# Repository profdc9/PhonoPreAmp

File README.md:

# Phono Preamplifier

This is a PCB for Bill Christie's phono preamplifier as detailed in his article "Build an External Phonograph Preamplifier" in the 07/13 issue of audioXpress.  The original article can be found at

https://audioxpress.com/article/You-Can-DIY-Build-an-External-Phono-Preamplifier

https://audioxpress.com/assets/upload/files/BillChristieExternalPhonoPreampAXJul2013.pdf

The changes made are as follows.  The LME49740, which is not available anymore, has been replaced with two LM4562 op amps.  22 pF Miller capacitors are placed to stabilize the LM4562 from oscillation.  The signal grounds for the two channels are isolated from the power ground by hum breaker resistors.

This is a two-channel PCB layout for the LM3886-based Super Gain Clone by Bob Cordell.  It can be found in Chapter 27 in his book "Audio Amplifiers."

The PCB is made available under the Creative Commons CC-BY-SA 4.0 license.

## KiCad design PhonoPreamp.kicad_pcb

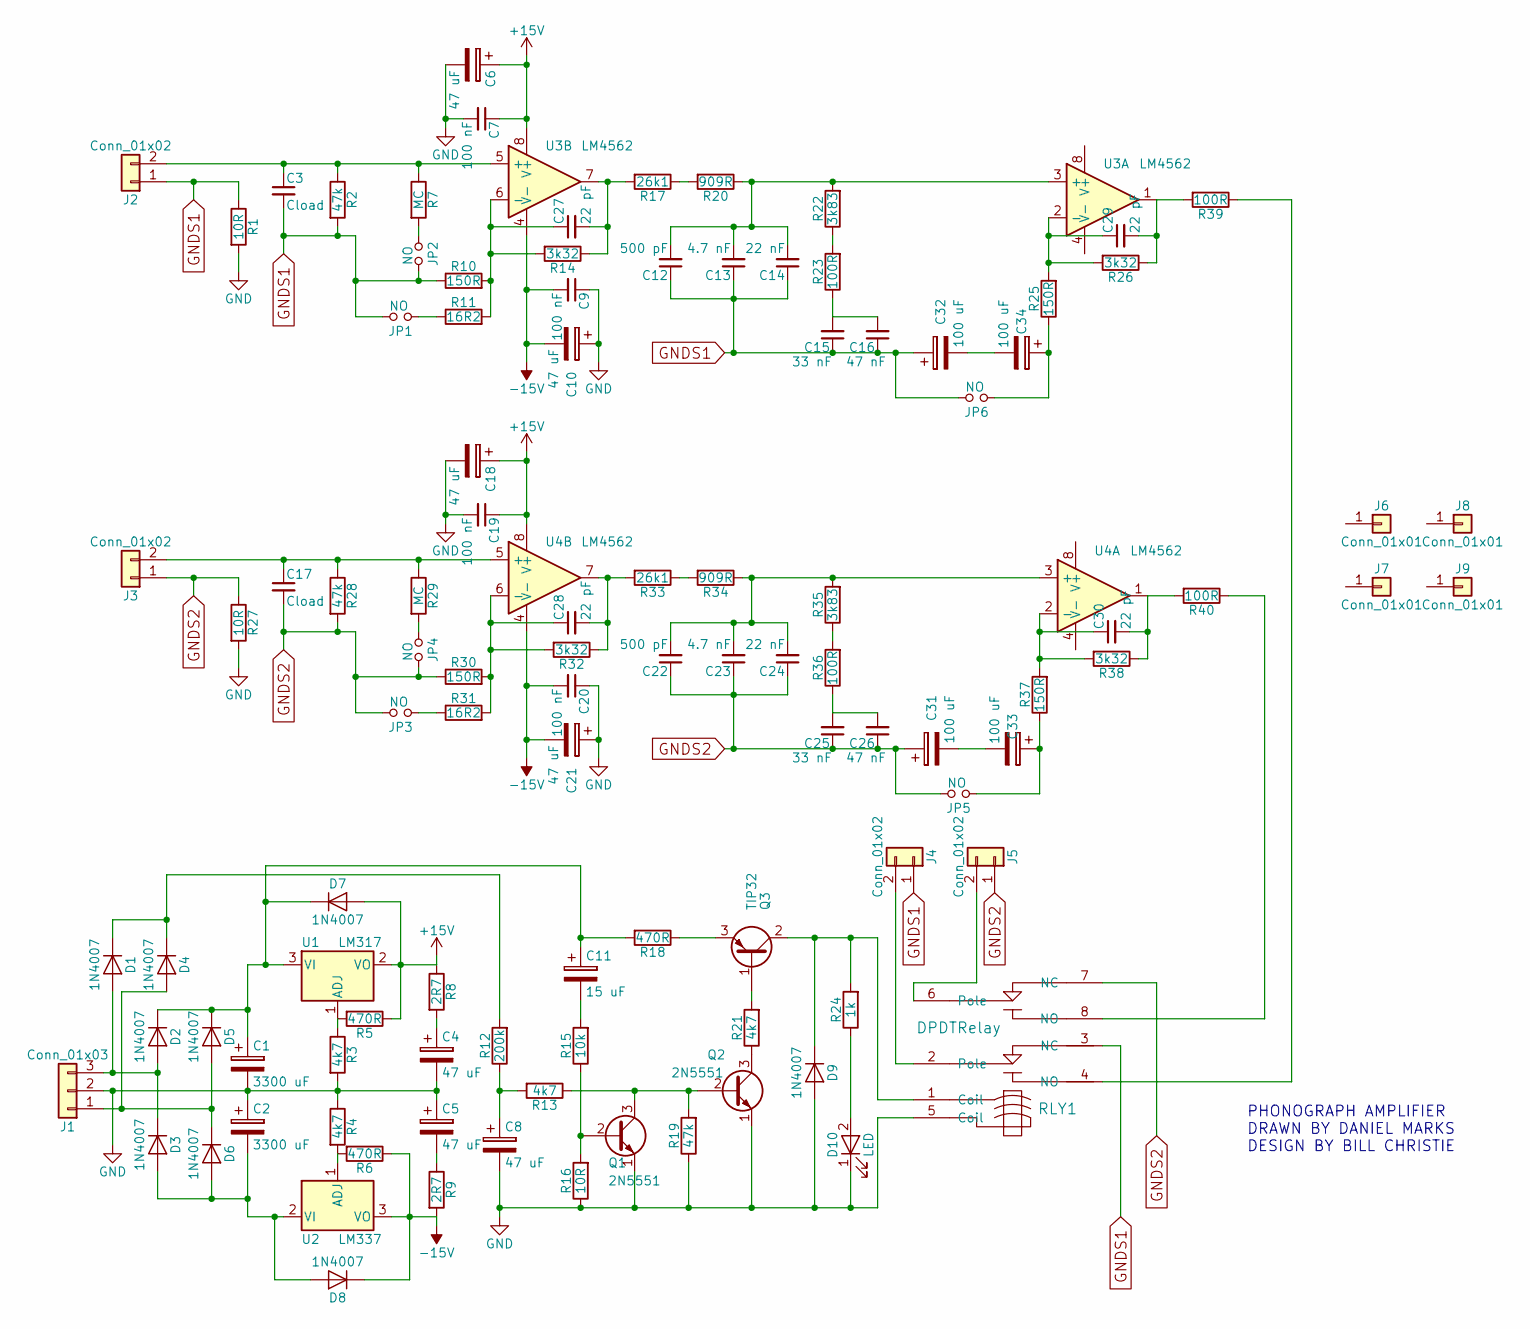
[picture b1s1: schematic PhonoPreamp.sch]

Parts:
C1, C2: 3300 uF; CP_Radial_D14.0mm_P5.00mm
C3, C17: Cload; C_Disc_D5.0mm_W2.5mm_P5.00mm
C4, C5: 47 uF; CP_Radial_D14.0mm_P5.00mm
C6, C8, C10, C18, C21: 47 uF; CP_Radial_D7.5mm_P2.50mm
C7, C9, C19, C20: 100 nF; C_Disc_D5.0mm_W2.5mm_P5.00mm
C11: 15 uF; CP_Radial_D7.5mm_P2.50mm
C12, C22: 500 pF; C_Disc_D5.0mm_W2.5mm_P5.00mm
C13, C23: 4.7 nF; C_Disc_D5.0mm_W2.5mm_P5.00mm
C14, C24: 22 nF; C_Disc_D5.0mm_W2.5mm_P5.00mm
C15, C25: 33 nF; C_Disc_D5.0mm_W2.5mm_P5.00mm
C16, C26: 47 nF; C_Disc_D5.0mm_W2.5mm_P5.00mm
C27, C28, C29, C30: 22 pF; C_Disc_D5.0mm_W2.5mm_P5.00mm
C31, C32, C33, C34: 100 uF; CP_Radial_D7.5mm_P2.50mm
D1, D2, D3, D4, D5, D6, D7, D8, D9: 1N4007; D_DO-41_SOD81_P7.62mm_Horizontal
D10: LED; LED_D5.0mm
J1: Conn_01x03; TerminalBlock_bornier-3_P5.08mm
J2, J3, J4, J5: Conn_01x02; TerminalBlock_bornier-2_P5.08mm
J6, J7, J8, J9: Conn_01x01; 1pin
JP1, JP2, JP3, JP4, JP5, JP6: NO; Pin_Header_Straight_1x02_Pitch2.54mm
Q1, Q2: 2N5551; TO-92_Inline_Wide
Q3: TIP32; TO-220-3_Vertical
R1, R16, R27: 10R; R_Axial_DIN0207_L6.3mm_D2.5mm_P7.62mm_Horizontal
R2, R19, R28: 47k; R_Axial_DIN0207_L6.3mm_D2.5mm_P7.62mm_Horizontal
R3, R4, R13, R21: 4k7; R_Axial_DIN0207_L6.3mm_D2.5mm_P7.62mm_Horizontal
R5, R6: 470R; R_Axial_DIN0207_L6.3mm_D2.5mm_P7.62mm_Horizontal
R7, R29: MC; R_Axial_DIN0207_L6.3mm_D2.5mm_P7.62mm_Horizontal
R8, R9: 2R7; R_Axial_DIN0207_L6.3mm_D2.5mm_P7.62mm_Horizontal
R10, R25, R30, R37: 150R; R_Axial_DIN0207_L6.3mm_D2.5mm_P7.62mm_Horizontal
R11, R31: 16R2; R_Axial_DIN0207_L6.3mm_D2.5mm_P7.62mm_Horizontal
R12: 200k; R_Axial_DIN0207_L6.3mm_D2.5mm_P7.62mm_Horizontal
R14, R26, R32, R38: 3k32; R_Axial_DIN0207_L6.3mm_D2.5mm_P7.62mm_Horizontal
R15: 10k; R_Axial_DIN0207_L6.3mm_D2.5mm_P7.62mm_Horizontal
R17, R33: 26k1; R_Axial_DIN0207_L6.3mm_D2.5mm_P7.62mm_Horizontal
R18: 470R; R_Axial_DIN0309_L9.0mm_D3.2mm_P12.70mm_Horizontal
R20, R34: 909R; R_Axial_DIN0207_L6.3mm_D2.5mm_P7.62mm_Horizontal
R22, R35: 3k83; R_Axial_DIN0207_L6.3mm_D2.5mm_P7.62mm_Horizontal
R23, R36, R39, R40: 100R; R_Axial_DIN0207_L6.3mm_D2.5mm_P7.62mm_Horizontal
R24: 1k; R_Axial_DIN0207_L6.3mm_D2.5mm_P7.62mm_Horizontal
RLY1: DPDTRelay; G2VRelay
U1: LM317; TO-220-3_Vertical
U2: LM337; TO-220-3_Vertical
U3, U4: LM4562; DIP-8_W7.62mm_Socket

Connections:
+15V: C6.1, C7.1, C18.1, C19.1, D7.2 (A), R5.1, R8.1, U1.2 (VO), U3.8 (V+), U4.8 (V+)
-15V: C9.2, C10.2, C20.2, C21.2, D8.1 (K), R6.1, R9.2, U2.3 (VO), U3.4 (V-), U4.4 (V-)
GND: C1.2, C2.1, C4.2, C5.1, C6.2, C7.2, C8.2, C9.1, C10.1, C18.2, C19.2, C20.1, C21.1, D9.2 (A), D10.1 (K), J1.2, Q1.1 (E), Q2.1 (E), R1.2, R3.2, R4.1, R16.1, R19.1, R27.2, RLY1.5 (Coil)
GNDS1: C3.2, C12.1, C13.1, C14.1, C15.1, C16.1, C32.1, J2.1, J4.1, JP1.2, JP2.2, JP6.2, R1.1, R2.2, R10.1, RLY1.3 (NC)
GNDS2: C17.2, C22.1, C23.1, C24.1, C25.1, C26.1, C31.1, J3.1, J5.1, JP3.2, JP4.2, JP5.2, R27.1, R28.2, R30.1, RLY1.7 (NC)
unnamed: C1.1, C11.1, D2.1 (K), D5.1 (K), D7.1 (K), R18.2, U1.3 (VI)
unnamed: C2.2, D3.2 (A), D6.2 (A), D8.2 (A), U2.2 (VI)
unnamed: C3.1, J2.2, R2.1, R7.1, U3.5 (+)
unnamed: C4.1, R8.2
unnamed: C5.2, R9.1
unnamed: C8.1, R12.1, R13.2
unnamed: C11.2, R15.2
unnamed: C12.2, C13.2, C14.2, R20.1, R22.2, U3.3 (+)
unnamed: C15.2, C16.2, R23.1
unnamed: C17.1, J3.2, R28.1, R29.1, U4.5 (+)
unnamed: C22.2, C23.2, C24.2, R34.1, R35.2, U4.3 (+)
unnamed: C25.2, C26.2, R36.1
unnamed: C27.1, R10.2, R11.2, R14.2, U3.6 (-)
unnamed: C27.2, R14.1, R17.2, U3.7
unnamed: C28.1, R30.2, R31.2, R32.2, U4.6 (-)
unnamed: C28.2, R32.1, R33.2, U4.7
unnamed: C29.1, R25.2, R26.2, U3.2 (-)
unnamed: C29.2, R26.1, R39.2, U3.1
unnamed: C30.1, R37.2, R38.2, U4.2 (-)
unnamed: C30.2, R38.1, R40.2, U4.1
unnamed: C31.2, C33.2
unnamed: C32.2, C34.2
unnamed: C33.1, JP5.1, R37.1
unnamed: C34.1, JP6.1, R25.1
unnamed: D1.1 (K), D4.1 (K), R12.2
unnamed: D1.2 (A), D2.2 (A), D3.1 (K), J1.3
unnamed: D4.2 (A), D5.2 (A), D6.1 (K), J1.1
unnamed: D9.1 (K), Q3.2 (C), R24.2, RLY1.1 (Coil)
unnamed: D10.2 (A), R24.1
unnamed: J4.2, RLY1.2 (Pole)
unnamed: J5.2, RLY1.6 (Pole)
unnamed: JP1.1, R11.1
unnamed: JP2.1, R7.2
unnamed: JP3.1, R31.1
unnamed: JP4.1, R29.2
unnamed: Q1.2 (B), R15.1, R16.2
unnamed: Q1.3 (C), Q2.2 (B), R13.1, R19.2
unnamed: Q2.3 (C), R21.1
unnamed: Q3.1 (B), R21.2
unnamed: Q3.3 (E), R18.1
unnamed: R3.1, R5.2, U1.1 (ADJ)
unnamed: R4.2, R6.2, U2.1 (ADJ)
unnamed: R17.1, R20.2
unnamed: R22.1, R23.2
unnamed: R33.1, R34.2
unnamed: R35.1, R36.2
unnamed: R39.1, RLY1.4 (NO)
unnamed: R40.1, RLY1.8 (NO)

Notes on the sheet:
PHONOGRAPH AMPLIFIER DRAWN BY DANIEL MARKS DESIGN BY BILL CHRISTIE

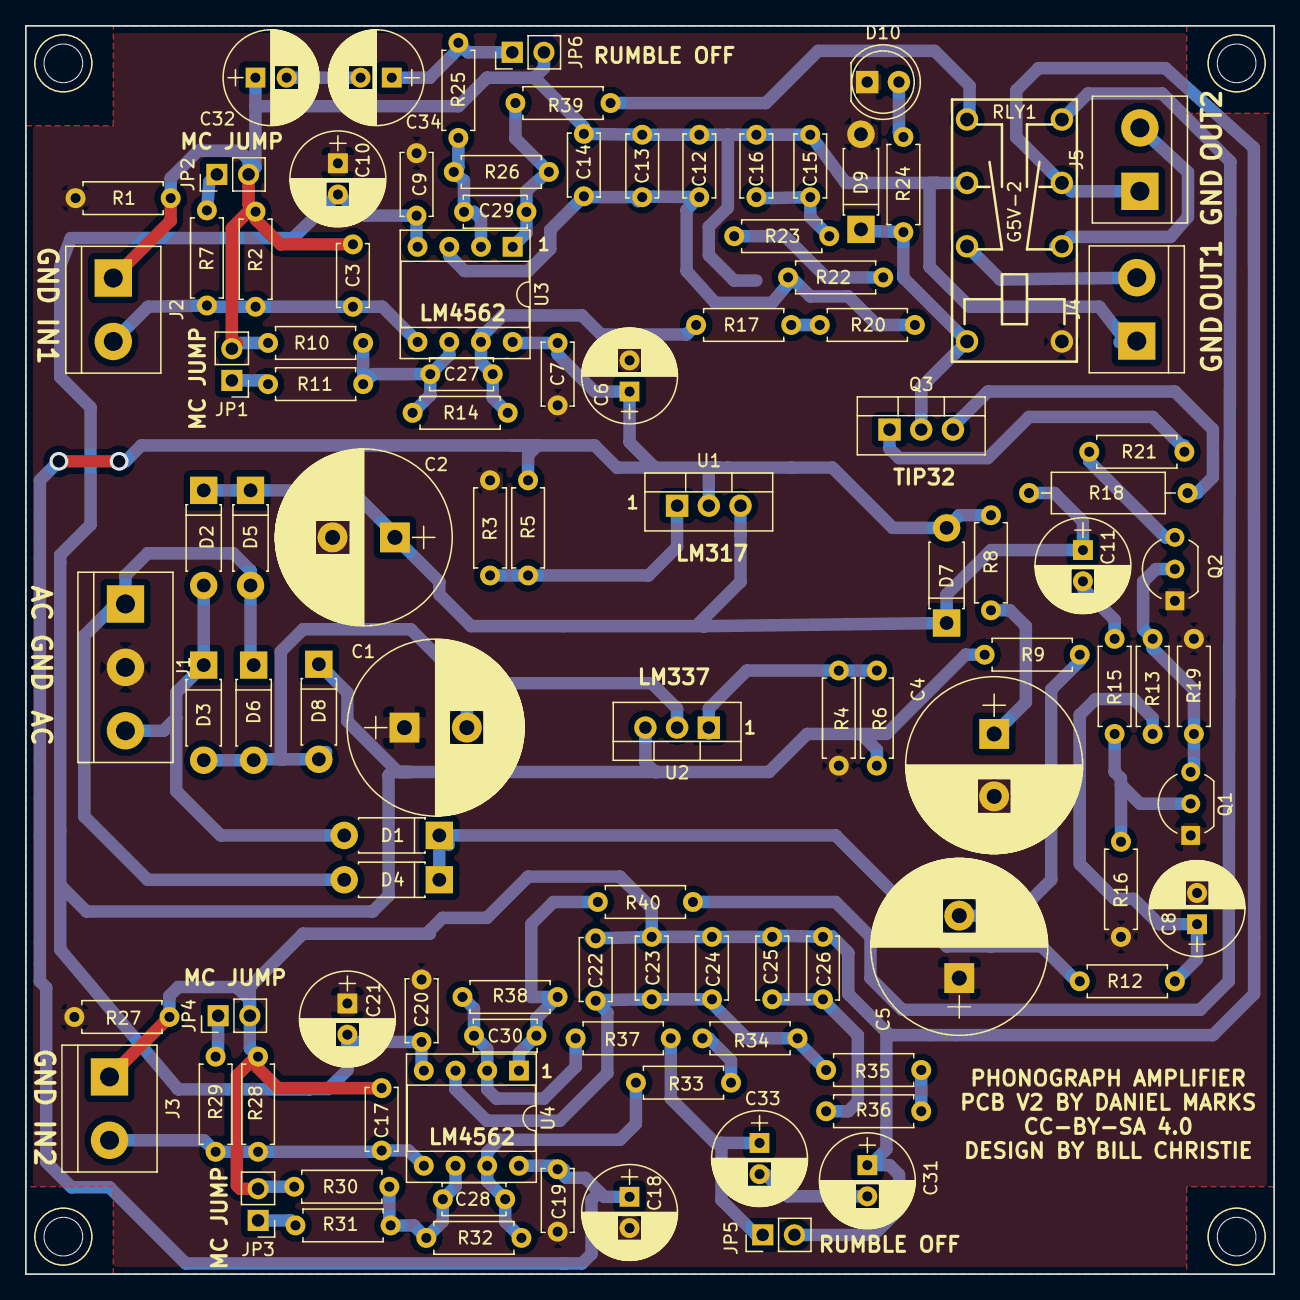
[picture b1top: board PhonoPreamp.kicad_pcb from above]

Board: 2 copper layers, 100.0 x 100.0 mm, 107 parts (0 on the bottom side), 53 nets.

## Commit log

2020-11-19 Made some space around capacitors
2021-05-28 Bigger capacitor footprints
2022-01-19 Added rumble filter
